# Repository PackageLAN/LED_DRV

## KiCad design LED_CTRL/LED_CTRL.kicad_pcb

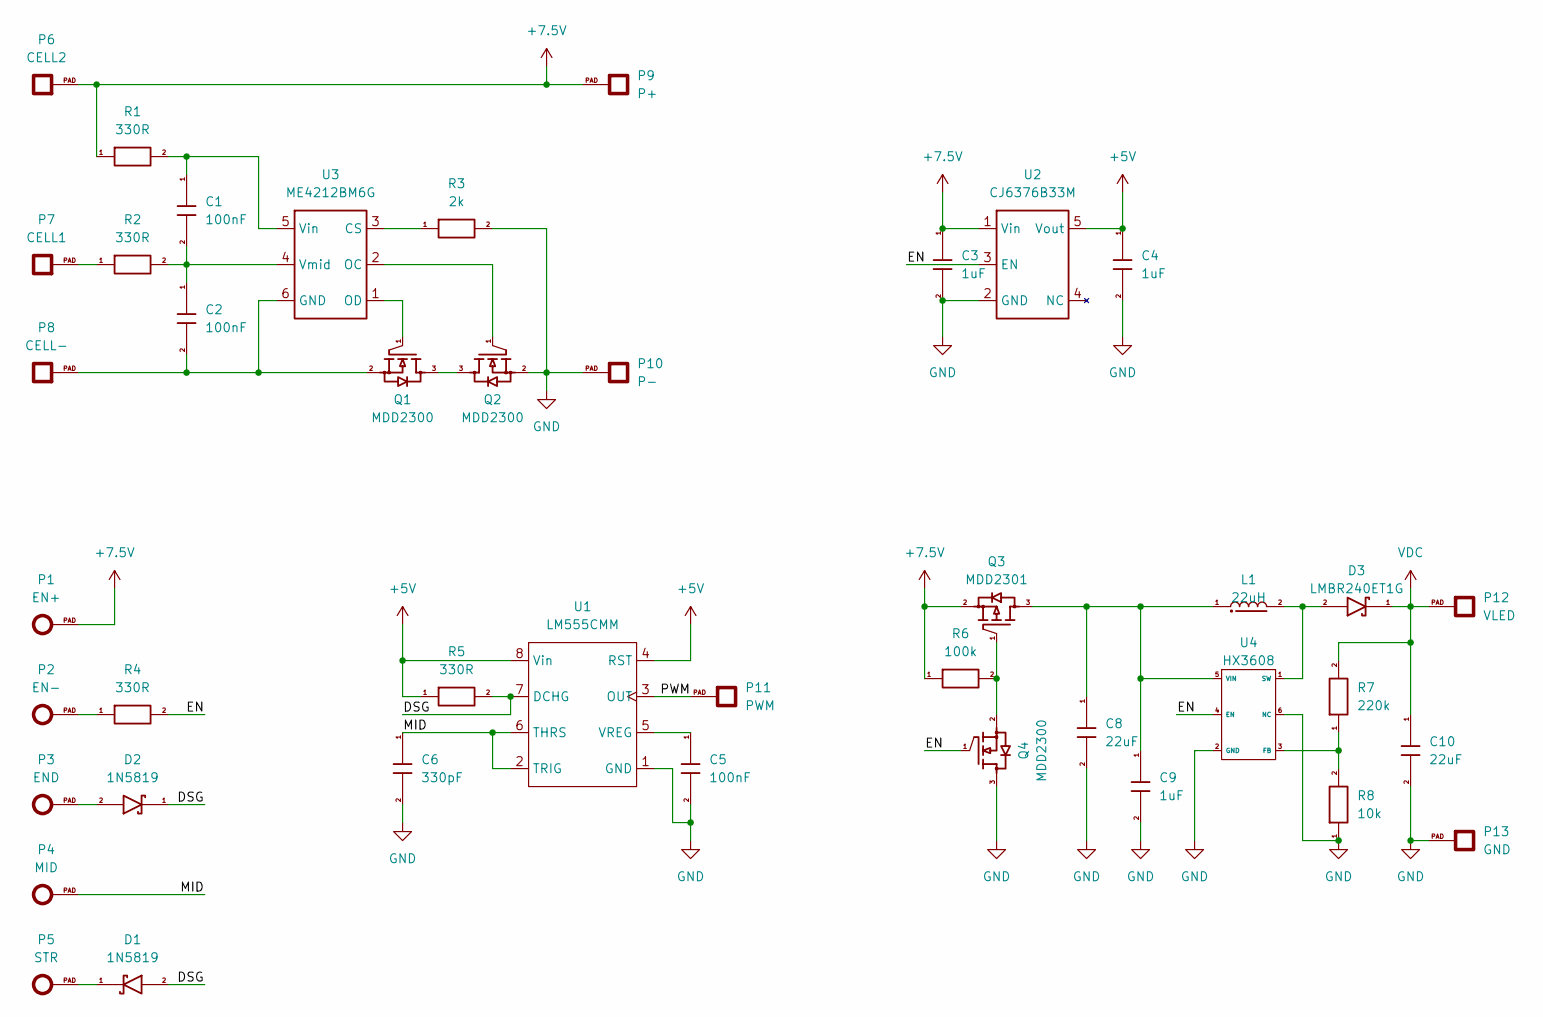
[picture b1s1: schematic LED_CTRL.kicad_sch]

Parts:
C1, C2, C5: 100nF; C0402(1005M)
C3, C4, C9: 1uF; C0402(1005M)
C6: 330pF; C0402(1005M)
C8, C10: 22uF; C0603(1608M)
D1, D2: 1N5819; SOD-323
D3: LMBR240ET1G; SOD-323HE
L1: 22uH; MC-2520
P1: EN+; SMP-C_15
P2: EN-; SMP-C_15
P3: END; SMP-C_15
P4: MID; SMP-C_15
P5: STR; SMP-C_15
P6: CELL2; SMP-Q_2020
P7: CELL1; SMP-Q_2020
P8: CELL-; SMP-Q_2020
P9: P+; SMP-Q_2020
P10: P-; SMP-Q_2020
P11: PWM; SMP-Q_2020
P12: VLED; SMP-Q_2020
P13: GND; SMP-Q_2020
Q1, Q2, Q4: MDD2300; SOT-23
Q3: MDD2301; SOT-23
R1, R2, R4, R5: 330R; R0402(1005M)
R3: 2k; R0402(1005M)
R6: 100k; R0402(1005M)
R7: 220k; R0402(1005M)
R8: 10k; R0402(1005M)
U1: LM555CMM; MSOP-8_3030
U2: CJ6376B33M; SOT-23-5; LCSC C427602
U3: ME4212BM6G; SOT-23-6
U4: HX3608; SOT-23-6

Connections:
+5V: C4.1, R5.1, U1.4 (RST), U1.8 (Vin), U2.5 (Vout)
+7.5V: C3.1, P1.PAD, P6.PAD, P9.PAD, Q3.2 (Source), R1.1, R6.1, U2.1 (Vin)
/DSG: D1.2 (Anode), D2.1 (Cathode), R5.2, U1.7 (DCHG)
/EN: Q4.1 (Gate), R4.2, U2.3 (EN), U4.4 (EN)
/MID: C6.1, P4.PAD, U1.2 (TRIG), U1.6 (THRS)
/PWM: P11.PAD, U1.3 (OUT)
GND: C3.2, C4.2, C5.2, C6.2, C8.2, C9.2, C10.2, P10.PAD, P13.PAD, Q2.2 (Source), Q4.3 (Drain), R3.2, R8.1, U1.1 (GND), U2.2 (GND), U4.2 (GND), U4.6 (NC)
unnamed: D1.1 (Cathode), P5.PAD
unnamed: D2.2 (Anode), P3.PAD
unnamed: D3.2 (Anode), L1.2, U4.1 (SW)
unnamed: P2.PAD, R4.1
unnamed: P7.PAD, R2.1
unnamed: Q1.3 (Drain), Q2.3 (Drain)
unnamed: Q1.1 (Gate), U3.1 (OD)
unnamed: C2.2, P8.PAD, Q1.2 (Source), U3.6 (GND)
unnamed: Q2.1 (Gate), U3.2 (OC)
unnamed: C8.1, C9.1, L1.1, Q3.3 (Drain), U4.5 (VIN)
unnamed: Q3.1 (Gate), Q4.2 (Source), R6.2
unnamed: C5.1, U1.5 (VREG)
unnamed: R3.1, U3.3 (CS)
unnamed: C1.1, R1.2, U3.5 (Vin)
unnamed: C1.2, C2.1, R2.2, U3.4 (Vmid)
unnamed: R7.1, R8.2, U4.3 (FB)
VDC: C10.1, D3.1 (Cathode), P12.PAD, R7.2

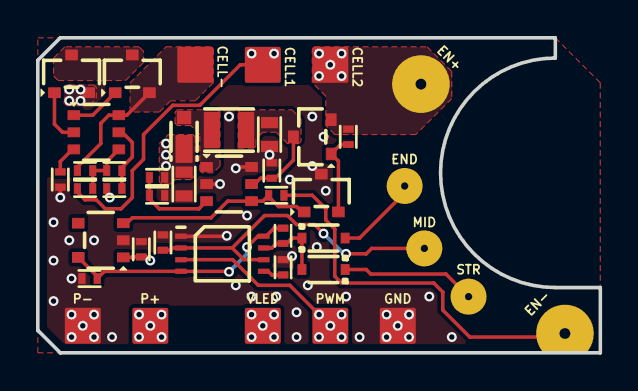
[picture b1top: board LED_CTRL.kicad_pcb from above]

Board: 2 copper layers, 31.2 x 17.5 mm, 42 parts (0 on the bottom side), 24 nets.

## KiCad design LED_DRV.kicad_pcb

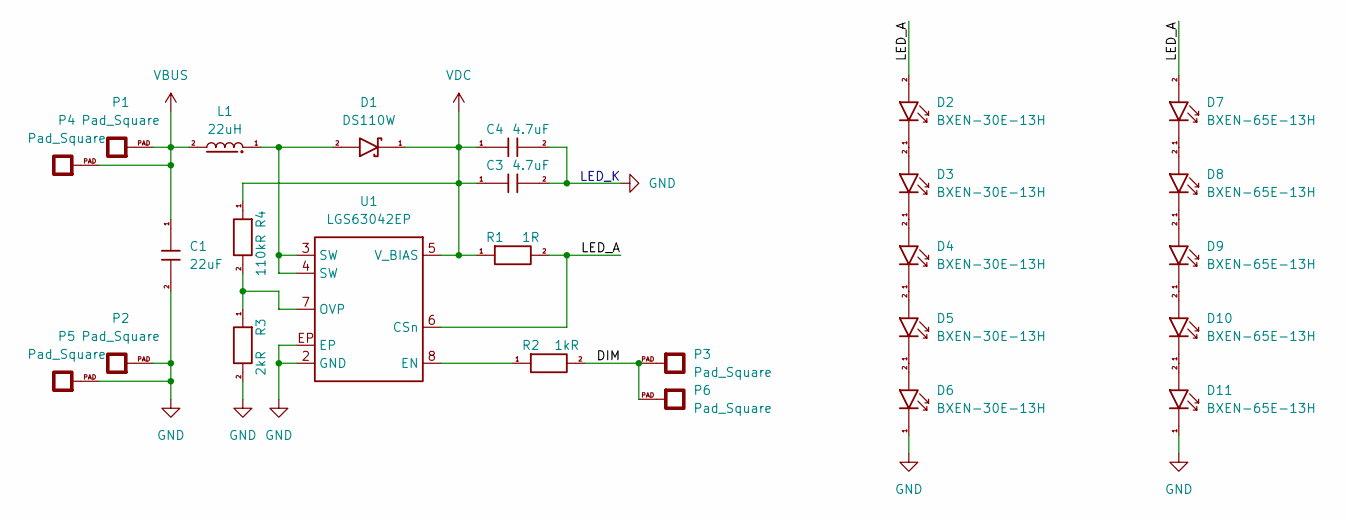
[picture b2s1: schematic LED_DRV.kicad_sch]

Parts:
C1: 22uF; C0805(2012M)
C3, C4: 4.7uF; C0805(2012M)
D1: DS110W; SOD-123F
D2, D3, D4, D5, D6: BXEN-30E-13H; LED2835M
D7, D8, D9, D10, D11: BXEN-65E-13H; LED2835M
L1: 22uH; MC-2520
P1, P2, P3, P4, P5, P6: Pad_Square; SMP-Q_2020
R1: 1R; R0603(1608M)
R2: 1kR; R0805(2012M)
R3: 2kR; R0603(1608M)
R4: 110kR; R0603(1608M)
U1: LGS63042EP; SOP-8EP_3949

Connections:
/DIM: P3.PAD, P6.PAD, R2.2
/LED_A: D2.2 (Anode), D7.2 (Anode), R1.2, U1.6 (CSn)
GND: C1.2, C3.2, C4.2, D6.1 (Cathode), D11.1 (Cathode), P2.PAD, P5.PAD, R3.2, U1.2 (GND), U1.EP
unnamed: D1.2 (Anode), L1.1, U1.3 (SW), U1.4 (SW)
unnamed: D2.1 (Cathode), D3.2 (Anode)
unnamed: D3.1 (Cathode), D4.2 (Anode)
unnamed: D4.1 (Cathode), D5.2 (Anode)
unnamed: D5.1 (Cathode), D6.2 (Anode)
unnamed: D7.1 (Cathode), D8.2 (Anode)
unnamed: D8.1 (Cathode), D9.2 (Anode)
unnamed: D9.1 (Cathode), D10.2 (Anode)
unnamed: D10.1 (Cathode), D11.2 (Anode)
unnamed: R2.1, U1.8 (EN)
unnamed: R3.1, R4.2, U1.7 (OVP)
VBUS: C1.1, L1.2, P1.PAD, P4.PAD
VDC: C3.1, C4.1, D1.1 (Cathode), R1.1, R4.1, U1.5 (V_BIAS)

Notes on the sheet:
LED_K

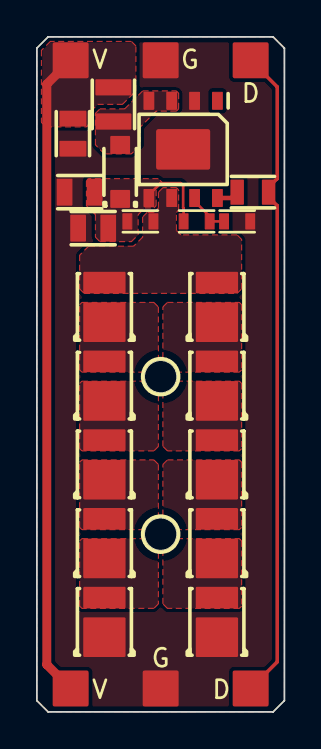
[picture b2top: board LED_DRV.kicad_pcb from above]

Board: 2 copper layers, 13.8 x 37.5 mm, 26 parts (0 on the bottom side), 16 nets.

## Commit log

2023-12-21 Add panel project.
2024-04-19 Daily update
2024-09-04 Update before RUN
